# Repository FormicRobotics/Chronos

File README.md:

<h1 align="center">⏱️ Chronos</h1>

<p align="center">
  <strong>Multi-Camera MIPI Synchronization System</strong><br>
  <em>Sub-microsecond synchronized capture for computer vision</em>
</p>

<p align="center">
  <a href="#-features">Features</a> •
  <a href="#-architecture">Architecture</a> •
  <a href="#-quick-start">Quick Start</a> •
  <a href="#-documentation">Documentation</a> •
  <a href="#-hardware">Hardware</a>
</p>

---

## ✨ Features

<table>
<tr>
<td width="50%">

### 🎯 Precision Synchronization
- **< 100ns** inter-camera trigger skew
- Hardware-triggered global shutter capture
- PLL-based timing generation
- Per-camera delay calibration

</td>
<td width="50%">

### 🚀 Zero-Copy GPU Pipeline
- Direct DMA to CUDA memory
- NvBuffer + EGL interop
- Triple-buffered capture
- No CPU memcpy overhead

</td>
</tr>
<tr>
<td width="50%">

### 📷 4-Camera Aggregation
- Single CSI-2 port for all cameras
- FPGA virtual channel multiplexing
- 1280×800 @ 120fps per camera
- 10-bit RAW global shutter

</td>
<td width="50%">

### 🔄 Integrated IMU
- BMI088 6-axis IMU
- Synchronized with cameras
- SPI @ 10MHz
- Timestamp correlation

</td>
</tr>
</table>

---

## 🏗️ Architecture

```
┌─────────────────────────────────────────────────────────────────────────┐
│                           CHRONOS SYSTEM                                 │
├─────────────────────────────────────────────────────────────────────────┤
│                                                                          │
│   ┌─────────┐ ┌─────────┐ ┌─────────┐ ┌─────────┐                       │
│   │  CAM 0  │ │  CAM 1  │ │  CAM 2  │ │  CAM 3  │     4× OV9281         │
│   │ OV9281  │ │ OV9281  │ │ OV9281  │ │ OV9281  │     Global Shutter    │
│   └────┬────┘ └────┬────┘ └────┬────┘ └────┬────┘                       │
│        │ CSI-2     │           │           │                             │
│        └───────────┴─────┬─────┴───────────┘                             │
│                          ▼                                               │
│   ┌──────────────────────────────────────────────┐                      │
│   │           CrossLink-NX FPGA                   │     Virtual Channel  │
│   │  ┌────────┐  ┌────────┐  ┌────────────────┐  │     Aggregation      │
│   │  │ 4× RX  │→ │ Buffer │→ │ TX + VC Tag    │  │                      │
│   │  └────────┘  └────────┘  └───────┬────────┘  │                      │
│   │  ┌─────────────────────────────┐ │           │                      │
│   │  │    Trigger Generator (PLL)  │─┼──────────────→ FSIN + IMU        │
│   │  └─────────────────────────────┘ │           │                      │
│   └──────────────────────────────────┼───────────┘                      │
│                                      │ Single 2-lane CSI-2              │
│                                      ▼                                   │
│   ┌──────────────────────────────────────────────────────────────┐      │
│   │                    Jetson Orin NX                             │      │
│   │  ┌─────────┐  ┌─────────┐  ┌─────────┐  ┌─────────────────┐  │      │
│   │  │  NVCSI  │→ │   VI    │→ │ Driver  │→ │   GPU Memory    │  │      │
│   │  │  D-PHY  │  │  DMA    │  │ Demux   │  │   (Zero-Copy)   │  │      │
│   │  └─────────┘  └─────────┘  └─────────┘  └─────────────────┘  │      │
│   └──────────────────────────────────────────────────────────────┘      │
│                                                                          │
└─────────────────────────────────────────────────────────────────────────┘
```

---

## 🚀 Quick Start

### Prerequisites

- NVIDIA Jetson Orin NX with JetPack 5.x
- Chronos PCB (CrossLink-NX FPGA board)
- 4× OV9281 camera modules
- CUDA Toolkit, CMake 3.18+

### Build & Install

```bash
# Clone the repository
git clone https://github.com/your-org/chronos.git
cd chronos

# Build kernel drivers
cd drivers
make all
sudo make install

# Build user-space applications
cd ../app
mkdir build && cd build
cmake ..
make -j$(nproc)
sudo make install
```

### Run Demo

```bash
# Load drivers
sudo modprobe ov9281
sudo modprobe chronos_csi

# Run synchronized capture demo
chronos_demo --rate 60 --exposure 5000

# Run synchronization validation
sync_test -n 1000 -r 120
```

### Example Output

```
Chronos Demo - 4-Camera Synchronized Capture
=============================================
Frame Rate: 60 fps
Exposure: 5000 us

FPS: 60.0  Sync: 1234
  IMU: Accel[  0.02,  -0.01,   9.81] m/s²  Gyro[  0.00,   0.00,   0.00] rad/s
  Frame Sync: Cam0:1234 Cam1:1234 Cam2:1234 Cam3:1234 [SYNC OK]
```

---

## 📁 Project Structure

```
chronos/
├── 📂 fpga/                    # FPGA Firmware
│   ├── 📂 rtl/                 # SystemVerilog sources
│   │   ├── chronos_top.sv      # Top-level module
│   │   ├── csi2_rx.sv          # CSI-2 receivers (×4)
│   │   ├── csi2_tx.sv          # CSI-2 transmitter
│   │   ├── frame_buffer.sv     # SRAM line buffers
│   │   ├── tx_arbiter.sv       # VC multiplexer
│   │   ├── trigger_generator.sv # Sync pulse generator
│   │   └── config_regs.sv      # I2C register bank
│   └── 📂 constraints/         # Timing/pin constraints
│
├── 📂 drivers/                 # Linux Kernel Modules
│   ├── 📂 ov9281/              # OV9281 V4L2 driver
│   ├── 📂 chronos_csi/         # CSI demux driver
│   ├── 📂 imu/                 # BMI088 IIO driver
│   └── chronos-orin-nx.dts     # Device tree overlay
│
├── 📂 app/                     # User-Space Applications
│   └── 📂 src/
│       ├── chronos_capture.h   # Capture library API
│       ├── chronos_capture.c   # Library implementation
│       ├── demo_app.cpp        # Demo application
│       └── sync_test.cpp       # Sync validation tool
│
└── 📂 docs/                    # Documentation
    ├── architecture.md         # System design
    ├── api_reference.md        # API documentation
    └── user_guide.md           # User manual
```

---

## 📖 Documentation

| Document | Description |
|----------|-------------|
| [📐 Architecture](docs/architecture.md) | System design, block diagrams, data flow |
| [📚 API Reference](docs/api_reference.md) | Complete C API documentation |
| [📘 User Guide](docs/user_guide.md) | Installation, usage, troubleshooting |
| [🤝 Contributing](CONTRIBUTING.md) | Development guidelines |

---

## 🔧 Hardware Specifications

| Component | Specification |
|-----------|---------------|
| **FPGA** | Lattice CrossLink-NX (LIFCL-40) |
| **Cameras** | 4× OV9281 (1280×800, global shutter) |
| **Interface** | MIPI CSI-2, 2-lane @ 800 Mbps/lane |
| **Output** | Single 2-lane CSI-2 (4 virtual channels) |
| **Sync Accuracy** | < 100 ns trigger skew |
| **Frame Rate** | 1–120 fps (configurable) |
| **IMU** | BMI088 / ICM-42688-P (6-axis) |
| **Power** | ~2.5W total |
| **Temperature** | -10°C to +55°C (commercial) |

---

## 📊 Performance

<table>
<tr>
<th>Metric</th>
<th>Value</th>
<th>Notes</th>
</tr>
<tr>
<td>Inter-camera sync</td>
<td><strong>< 100 ns</strong></td>
<td>99th percentile</td>
</tr>
<tr>
<td>Capture-to-GPU latency</td>
<td><strong>< 5 ms</strong></td>
<td>Zero-copy path</td>
</tr>
<tr>
<td>Max frame rate</td>
<td><strong>120 fps</strong></td>
<td>All 4 cameras</td>
</tr>
<tr>
<td>Aggregate throughput</td>
<td><strong>1.2 Gbps</strong></td>
<td>4× RAW10 streams</td>
</tr>
<tr>
<td>Frame drop rate</td>
<td><strong>< 0.01%</strong></td>
<td>Triple-buffered</td>
</tr>
</table>

---

## 🛠️ API Example

```c
#include <chronos_capture.h>

int main() {
    // Initialize
    chronos_init();
    
    // Configure synchronized capture
    chronos_config_t config = {
        .frame_rate = 60,
        .exposure_us = 5000,
        .external_trigger = true,
        .enable_imu = true,
    };
    chronos_configure(&config);
    
    // Capture loop
    chronos_start_capture();
    while (running) {
        chronos_sync_frame_set_t frames;
        
        if (chronos_get_frame_set(&frames, 1000) == CHRONOS_OK) {
            // Get CUDA pointer (zero-copy!)
            void *gpu_ptr;
            chronos_get_cuda_ptr(&frames.frames[0], &gpu_ptr);
            
            // Run your CUDA kernels here...
            
            chronos_release_frame_set(&frames);
        }
    }
    
    chronos_shutdown();
    return 0;
}
```

---

## 📜 License

| Component | License |
|-----------|---------|
| FPGA Firmware | Proprietary |
| Linux Drivers | GPL v2 |
| User Applications | MIT |

---

## 👥 Authors

**Umit Kayacik** — *Senior Electronics Engineer*

---

<p align="center">
  <em>Built with ❤️ for computer vision applications</em>
</p>

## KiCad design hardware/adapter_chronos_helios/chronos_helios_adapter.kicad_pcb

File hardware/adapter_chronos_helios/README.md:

# Chronos J7 <-> Aerium Helios CAM1 adapter PCB (v3)

Small (28 x 28 mm, 4-layer) adapter that safely connects the Chronos board's
custom 22-pin CSI output (J7) to the Aerium Helios carrier's standard
Raspberry-Pi-style 15-pin CAM1 port. A direct cable between the two is **not**
possible: J7 uses a custom pinout (SDA/SCL order reversed, 3.3V on pins 19/20,
GND on pin 15) that would short Helios 3.3V to GND and put 3.3V on I2C lines.

**v3 change (pin-1 orientation verified on hardware):** with the two boards
face to face and flat cables, **both pin 1s sit on the same absolute side**
(user-verified on the physical boards, 2026-07). The Chronos link mirrors
through its cable as normal facing FH12s do (J7 pin i lands on J1 pad 23-i),
but the Helios CAM1 connector is opposite-handed, so its link maps **straight**
(CAM1 pin j lands on J2 pad j). The two effects nearly cancel: v3 routes all
six CSI conductors as identical straight diagonals on the top layer with
**zero vias**, and only the I2C SDA/SCL swap needs one inner-layer crossing.

Open `chronos_helios_adapter.kicad_pcb` in KiCad 10 (board file is the source
of truth; there is no schematic - the netlist lives in the board).
DRC: 0 errors / 0 unconnected items; only informational "library footprint
mismatch" warnings remain (universal mounting-tab pads, see `drc_report.txt`).

## Connections

```
CHRONOS J7                      ADAPTER                       HELIOS CAM1
(22p custom)  straight 22p   J1 <- remap -> J2     straight 15p   (15p RPi std)
    [J7] ==== Type-A FFC ==== [J1]          [J2] ==== Type-A FFC ==== [CAM1]
              (mirrors i->23-i)              (straight j->j)
```

- **J1** (22P 0.5 mm bottom contact, FH12-22S / XUNPU FPC-05F-22PH20): to
  Chronos J7 with a **straight 22-pin 0.5 mm Type-A (same-side contacts) FFC**.
  Facing receptacles mirror the mapping through the cable (J7 pin i lands on
  J1 pad 23-i); the netlist accounts for this.
- **J2** (15P 0.5 mm bottom contact, FH12-15S / XFCN F0502-B-15-15T-R): to
  Helios CAM1 with a **straight 15-pin 0.5 mm Type-A FFC**. The Helios CAM
  connector is opposite-handed (pin 1 on the same absolute side as J7's, as
  verified on the hardware), so this link maps **straight**: CAM1 pin j lands
  on J2 pad j, baked into the netlist.
- Net result on the board: every CSI net leaves J1 and reaches J2 shifted a
  constant 1.75 mm sideways - all six conductors are equal-length top-layer
  diagonals (no vias, no skew). Only SDA crosses SCL once, on inner layer
  In2.Cu over the solid B.Cu ground plane.

### Signal map

| Function | Chronos J7 | Adapter J1 pad | Adapter J2 pad | Helios CAM1 (15p) |
|---|---|---|---|---|
| CSI D0- / D0+ | 2 / 3 | 21 / 20 | 2 / 3 | 2 / 3 |
| CSI D1- / D1+ | 5 / 6 | 18 / 17 | 5 / 6 | 5 / 6 |
| CSI CLK- / CLK+ | 8 / 9 | 15 / 14 | 8 / 9 | 8 / 9 |
| I2C SDA | 13 | 10 | 14 | 14 |
| I2C SCL | 14 | 9 | 13 | 13 |
| Chronos 3.3V | 19, 20 | 3, 4 | - (TP1 / SJ1 only) | - |
| Helios 3.3V | - | - | 15 (TP2 / SJ1 only) | 15 |
| SENSE (orientation check) | - | - | 1 (TP3 only) | 1 (GND) |
| GND | 1,4,7,10,12,15,18,21,22 | 1,2,5,8,11,13,16,22 | 4,7,10 | 4,7,10 |

The I2C swap (Chronos has SDA=13/SCL=14, RPi standard has SCL=13/SDA=14) is
done on the adapter. The two 3.3V rails are **never** connected to each other:
SJ1 solder jumper stays **OPEN** (each board powers itself). J1 pad 19 is left
unconnected on purpose (safety if a wrong cable type is used), and J2 pad 1
is the SENSE_H net (TP3 only) - in the correct orientation it sees CAM1 GND;
with a wrong/mirror cable it would see CAM1 3.3V harmlessly.

## Bring-up / polarity verification (do this BEFORE full hookup)

FFC orientation mistakes are the only real risk; the board is designed so a
wrong cable type causes no damage and is detectable:

1. **Chronos side**: power Chronos (USB), connect only J7 -> J1 with the 22p
   cable. Measure **TP1 (3V3C)**: must read **3.3 V** (and TP4 = GND beeps to
   Chronos ground). If TP1 does not read 3.3 V, the cable is the wrong
   contact type - swap the 22p cable between Type-A (same-side) and Type-B
   (reverse/opposite-side). Keep this wrong-state power-on brief.
2. **Helios side**: with Chronos disconnected, power Helios, connect CAM1 ->
   J2 with the 15p cable. Measure **TP2 (V33H)**: must read **3.3 V**, and
   **TP3 (SENS)** must beep to ground. If instead TP3 shows 3.3 V and TP2
   reads 0, the cable is the wrong contact type - swap the 15p cable between
   Type-A and Type-B.
3. Only after both checks pass, connect everything together (SJ1 open).

Cables must lie **flat** between the boards (no folds or twists) - a folded
FFC flips the mapping and will show up in the TP checks above.

## Differential pair design (100 ohm, MIPI D-PHY)

Stackup: **4-layer 1.6 mm, JLCPCB JLC04161H-7628** (or equivalent):
L1 signal / L2 GND plane / L3 (SDA crossing only) / L4 GND plane.
Outer prepreg 7628 = 0.21 mm on both sides, Er ~ 4.4/4.6.

- All six CSI conductors run on **L1 over the L2 plane** for their entire
  length: w = 0.20 mm, pair pitch 0.5 mm at the pads (Zdiff ~ 105-117 ohm,
  within the 80-125 ohm D-PHY tolerance), total length ~9.6 mm (~65 ps),
  **zero vias**, and all six diagonals are geometrically identical so
  intra-pair and inter-pair skew are both zero by construction.
- I2C: SCL runs on L1; SDA dives to **In2.Cu (L3)** through two 0.5/0.3 mm
  vias to cross SCL (no impedance requirement at 400 kHz).
- In2.Cu carries nothing else and has no copper pour; In1.Cu and B.Cu are
  solid GND zones stitched with 0.6/0.3 mm vias.

**When ordering choose "Impedance control: JLC04161H-7628"** and keep L2/L4
as the solid GND planes.

## Mechanical

- 4x M2 mounting holes (H1-H4, 2.2 mm NPTH) in the corners, centers 2.3 mm
  from each edge - fits M2 screws + standoffs.
- Both connectors have 3D models assigned (KiCad standard lib FH12 models),
  so the 3D viewer (Alt+3) shows the assembled board.
- Cable exits: J2 opening faces the top edge (toward Helios), J1 opening
  faces the bottom edge (toward Chronos).

## Fabrication at JLCPCB (verified 2026-07)

Ready-to-upload outputs are in `fab/`:

- `chronos_helios_adapter_gerbers.zip` - Gerbers + Excellon drills (upload as-is)
- `jlc_bom.csv` / `jlc_cpl.csv` - BOM and CPL in JLC assembly format

Order options:

- **Layers 4, thickness 1.6 mm**, and set **Impedance Control: yes ->
  JLC04161H-7628**. Layer order in the zip: `.gtl` = L1, `.g1` = L2 (GND),
  `.g2` = L3 (SDA crossing), `.gbl` = L4 (GND).
- Everything is inside standard capabilities (checked against JLC 4-layer
  rules): min track/gap used 0.20/0.15 mm (cap. 0.09/0.09), signal vias
  0.5/0.3 mm and GND vias 0.6/0.3 mm (cap. 0.45/0.2), NPTH 2.2 mm,
  copper-to-edge >= 0.3 mm outer / 0.4 mm inner, silkscreen >= 0.8 mm text.
- LeadFree/HASL either is fine; ENIG is nicer for the 0.5 mm pads but not
  required.

### Connectors (BOM check)

Genuine Hirose FH12 parts are out of stock at LCSC, so the BOM uses
pin-compatible clones (both in stock, JLC "Extended" parts):

- **J1: XUNPU FPC-05F-22PH20, LCSC C2856804** - 22P 0.5 mm bottom-contact,
  hinged-lid ZIF for 0.3 mm FFC (~$0.10/pc, MOQ 5).
- **J2: XFCN F0502-B-15-15T-R, LCSC C2844857** - 15P 0.5 mm bottom-contact,
  hinged-lid ZIF for 0.3 mm FFC (in stock ~2.4k pcs).
- Mounting-tab pads on both footprints are **enlarged to 2.1 x 2.9 mm** to
  cover the tab positions of both the Hirose originals and the clones - so
  either brand solders onto this board.
- If you prefer genuine Hirose (FH12-22S-0.5SH(55) / FH12-15S-0.5SH(55)),
  buy from Mouser/DigiKey and hand-solder; nothing changes on the PCB.
- In the JLC assembly preview, verify the connector **opening faces the board
  edge** (cable exits outward) on both J1 and J2; fix rotation in their tool
  if their part library orientation differs.

TPs, SJ1 and H1-H4 are bare copper/holes - no other parts to source.

### Cables (both plain, no special Aerium cable)

- 1x **22-pin 0.5 mm Type-A** (same-side contacts) FFC, ~50-100 mm.
- 1x **15-pin 0.5 mm Type-A** (same-side contacts) FFC, ~50-100 mm.
- Order one Type-B (reverse) of each as insurance - they cost cents (LCSC
  custom cables, MOQ 1). The TP checks above tell you which type is right
  without risking damage.

## Files

- `chronos_helios_adapter.kicad_pcb` - the board (open in KiCad 10)
- `chronos_helios_adapter.kicad_pro` - project file (incl. CSI_100R netclass)
- `drc_report.txt` - last DRC run (0 errors, footprint-lib warnings only)
- `render_top.png` / `render_3d.png` - previews
- `fab/` - JLCPCB-ready Gerber zip, drills, BOM (`jlc_bom.csv`),
  CPL (`jlc_cpl.csv`)
- `_gen_v3.py` / `_fill_zones.py` - generator scripts used to build the board
- `_check_map.py` - end-to-end J7 -> CAM1 signal-map verification (PASS)

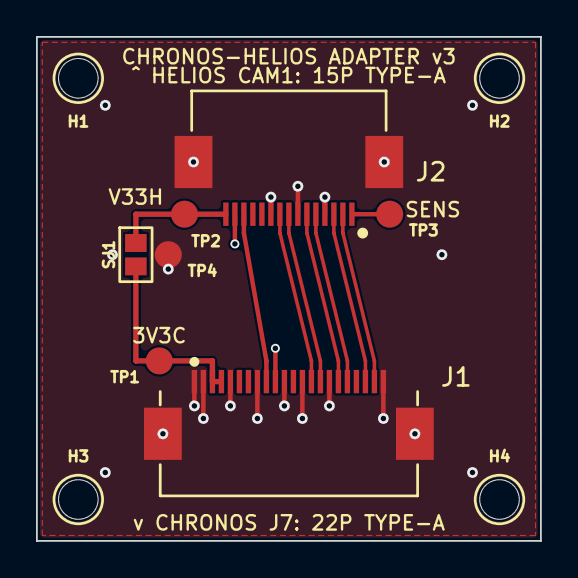
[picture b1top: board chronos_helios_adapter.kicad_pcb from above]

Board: 4 copper layers, 28.0 x 28.0 mm, 11 parts (0 on the bottom side), 12 nets.

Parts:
H1, H2, H3, H4: M2; MountingHole_2.2mm_M2
J1: FPC-05F-22PH20; Hirose_FH12-22S-0.5SH_1x22-1MP_P0.50mm_Horizontal
J2: F0502-B-15-15T-R; Hirose_FH12-15S-0.5SH_1x15-1MP_P0.50mm_Horizontal
SJ1: OPEN; SolderJumper-2_P1.3mm_Open
TP1: 3V3_CHRONOS; TestPoint_Pad_D1.5mm
TP2: 3V3_HELIOS; TestPoint_Pad_D1.5mm
TP3: SENSE_H; TestPoint_Pad_D1.5mm
TP4: GND; TestPoint_Pad_D1.5mm

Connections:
CSI_CLK_N: J1.15, J2.8
CSI_CLK_P: J1.14, J2.9
CSI_D0_N: J1.21, J2.2
CSI_D0_P: J1.20, J2.3
CSI_D1_N: J1.18, J2.5
CSI_D1_P: J1.17, J2.6
GND: J1.1, J1.2, J1.5, J1.8, J1.11, J1.13, J1.16, J1.22, J1.MP, J2.4, J2.7, J2.10, J2.MP, TP4.1
I2C_SCL: J1.9, J2.13
I2C_SDA: J1.10, J2.14
SENSE_H: J2.1, TP3.1
V33_CHRONOS: J1.3, J1.4, SJ1.1, TP1.1
V33_HELIOS: J2.15, SJ1.2, TP2.1

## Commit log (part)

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2026-01-25 Complete Chronos firmware implementation with modern README files - FPGA firmware, Linux drivers, capture library, demo apps, and documentation
2026-02-09 Hardware updated
2026-02-17 Hardware updated according to review items
2026-02-23 Hardware production files are ready.
